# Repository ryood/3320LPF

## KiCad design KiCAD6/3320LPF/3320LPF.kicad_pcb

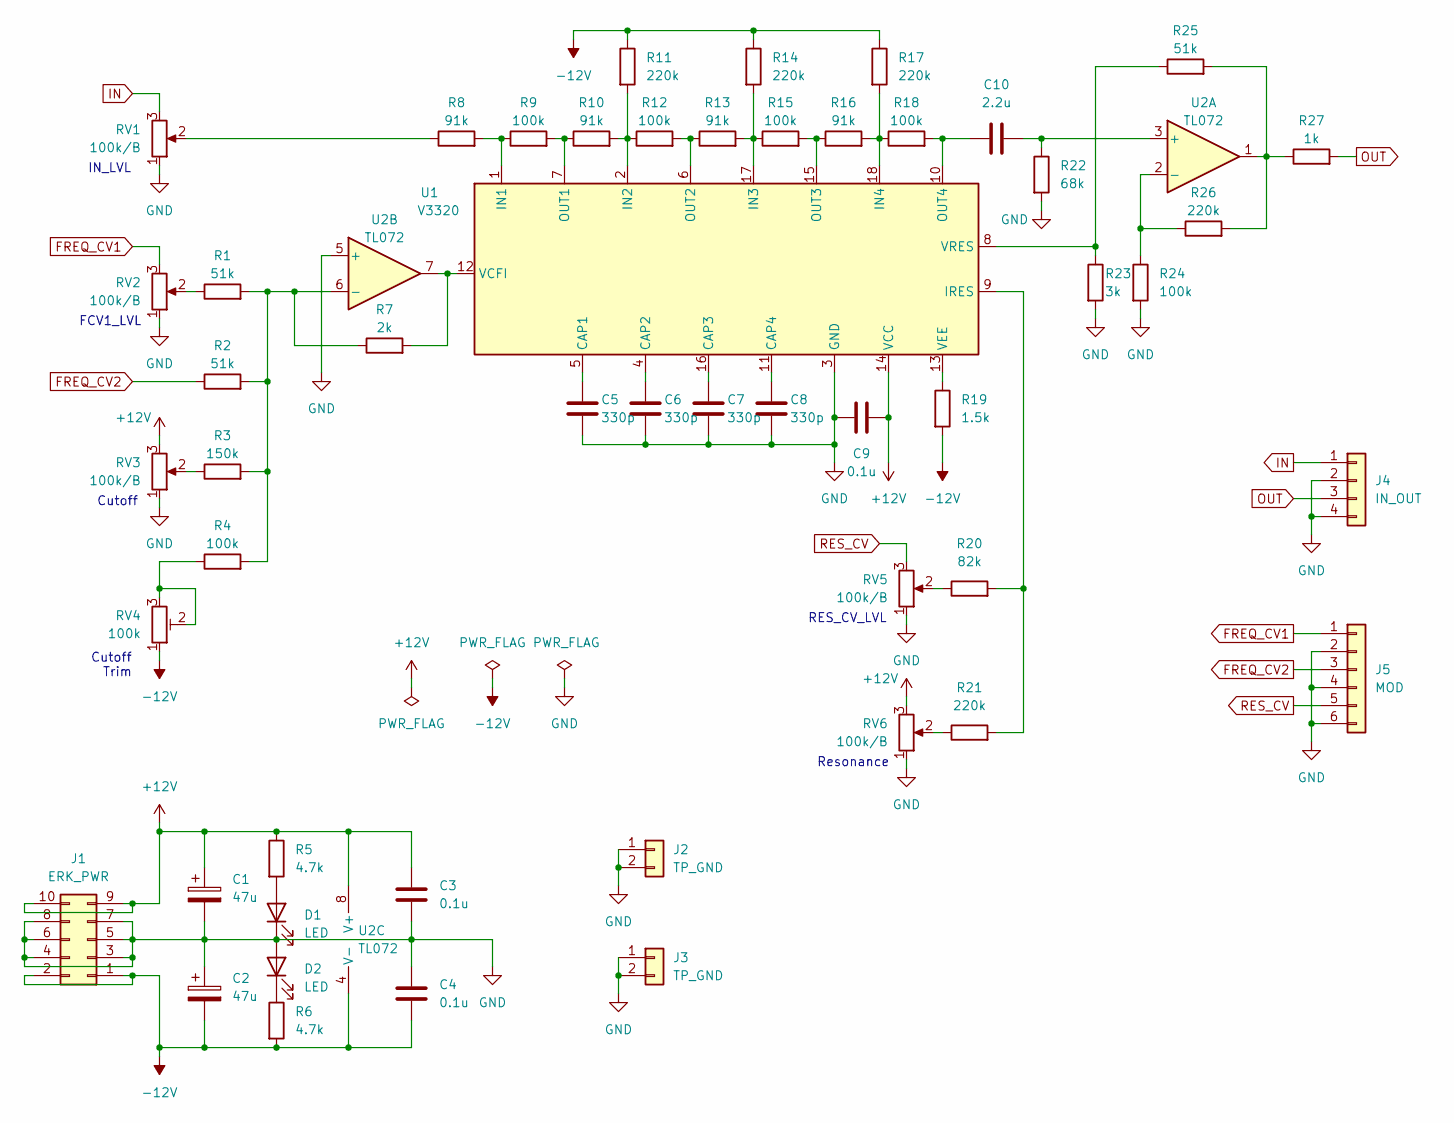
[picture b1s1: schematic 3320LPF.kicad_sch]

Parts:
C1, C2: 47u; CP_Radial_D5.0mm_P2.50mm
C3, C4, C9: 0.1u; C_Disc_D3.0mm_W1.6mm_P2.50mm
C5, C6, C7, C8: 330p; C_Rect_L7.0mm_W3.5mm_P5.00mm
C10: 2.2u; C_Rect_L7.2mm_W7.2mm_P5.00mm_FKS2_FKP2_MKS2_MKP2
D1, D2: LED; LED_D3.0mm
J1: ERK_PWR; IDC-Header_2x05_P2.54mm_Vertical
J2, J3: TP_GND; PinHeader_1x02_P2.54mm_Vertical
J4: IN_OUT; JST_XH_B4B-XH-A_1x04_P2.50mm_Vertical
J5: MOD; JST_XH_B6B-XH-A_1x06_P2.50mm_Vertical
R1, R2, R25: 51k; R_Axial_DIN0207_L6.3mm_D2.5mm_P10.16mm_Horizontal
R3: 150k; R_Axial_DIN0207_L6.3mm_D2.5mm_P10.16mm_Horizontal
R4, R9, R12, R15, R18, R24: 100k; R_Axial_DIN0207_L6.3mm_D2.5mm_P10.16mm_Horizontal
R5, R6: 4.7k; R_Axial_DIN0207_L6.3mm_D2.5mm_P10.16mm_Horizontal
R7: 2k; R_Axial_DIN0207_L6.3mm_D2.5mm_P10.16mm_Horizontal
R8, R10, R13, R16: 91k; R_Axial_DIN0207_L6.3mm_D2.5mm_P10.16mm_Horizontal
R11, R14, R17, R21, R26: 220k; R_Axial_DIN0207_L6.3mm_D2.5mm_P10.16mm_Horizontal
R19: 1.5k; R_Axial_DIN0207_L6.3mm_D2.5mm_P10.16mm_Horizontal
R20: 82k; R_Axial_DIN0207_L6.3mm_D2.5mm_P10.16mm_Horizontal
R22: 68k; R_Axial_DIN0207_L6.3mm_D2.5mm_P10.16mm_Horizontal
R23: 3k; R_Axial_DIN0207_L6.3mm_D2.5mm_P10.16mm_Horizontal
R27: 1k; R_Axial_DIN0207_L6.3mm_D2.5mm_P10.16mm_Horizontal
RV1, RV2, RV3, RV5, RV6: 100k/B; Potentiometer_Alps_RK09Y11_Single_Horizontal
RV4: 100k; Potentiometer_Bourns_3362P_Vertical
U1: V3320; DIP-18_W15.24mm
U2: TL072; DIP-8_W7.62mm_Socket

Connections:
+12V: C1.1, C3.1, C9.2, J1.9, J1.10, R5.1, RV3.3, RV6.3, U1.14 (VCC), U2.8 (V+)
-12V: C2.2, C4.2, J1.1, J1.2, R6.2, R11.1, R14.1, R17.1, R19.2, RV4.1, U2.4 (V-)
FREQ_CV1: J5.1, RV2.3
FREQ_CV2: J5.3, R2.1
GND: C1.2, C2.1, C3.2, C4.1, C5.2, C6.2, C7.2, C8.2, C9.1, D1.1 (K), D2.2 (A), J1.3, J1.4, J1.5, J1.6, J1.7, J1.8, J2.1, J2.2, J3.1, J3.2, J4.2, J4.4, J5.2, J5.4, J5.6, R22.2, R23.2, R24.2, RV1.1, RV2.1, RV3.1, RV5.1, RV6.1, U1.3 (GND), U2.5 (+)
IN: J4.1, RV1.3
unnamed: C5.1, U1.5 (CAP1)
unnamed: C6.1, U1.4 (CAP2)
unnamed: C7.1, U1.16 (CAP3)
unnamed: C8.1, U1.11 (CAP4)
unnamed: C10.1, R18.2, U1.10 (OUT4)
unnamed: C10.2, R22.1, U2.3 (+)
unnamed: D2.1 (K), R6.1
unnamed: R1.1, RV2.2
unnamed: R1.2, R2.2, R3.2, R4.2, R7.1, U2.6 (-)
unnamed: R3.1, RV3.2
unnamed: R4.1, RV4.2, RV4.3
unnamed: D1.2 (A), R5.2
unnamed: R7.2, U1.12 (VCFI), U2.7
unnamed: R8.1, RV1.2
unnamed: R8.2, R9.1, U1.1 (IN1)
unnamed: R9.2, R10.1, U1.7 (OUT1)
unnamed: R10.2, R11.2, R12.1, U1.2 (IN2)
unnamed: R12.2, R13.1, U1.6 (OUT2)
unnamed: R13.2, R14.2, R15.1, U1.17 (IN3)
unnamed: R15.2, R16.1, U1.15 (OUT3)
unnamed: R16.2, R17.2, R18.1, U1.18 (IN4)
unnamed: R19.1, U1.13 (VEE)
unnamed: R20.1, RV5.2
unnamed: R20.2, R21.2, U1.9 (IRES)
unnamed: R21.1, RV6.2
unnamed: R23.1, R25.1, U1.8 (VRES)
unnamed: R24.1, R26.1, U2.2 (-)
unnamed: R25.2, R26.2, R27.1, U2.1
OUT: J4.3, R27.2
RES_CV: J5.5, RV5.3

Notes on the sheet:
Resonance
Cutoff
Cutoff Trim
RES_CV_LVL
IN_LVL
FCV1_LVL

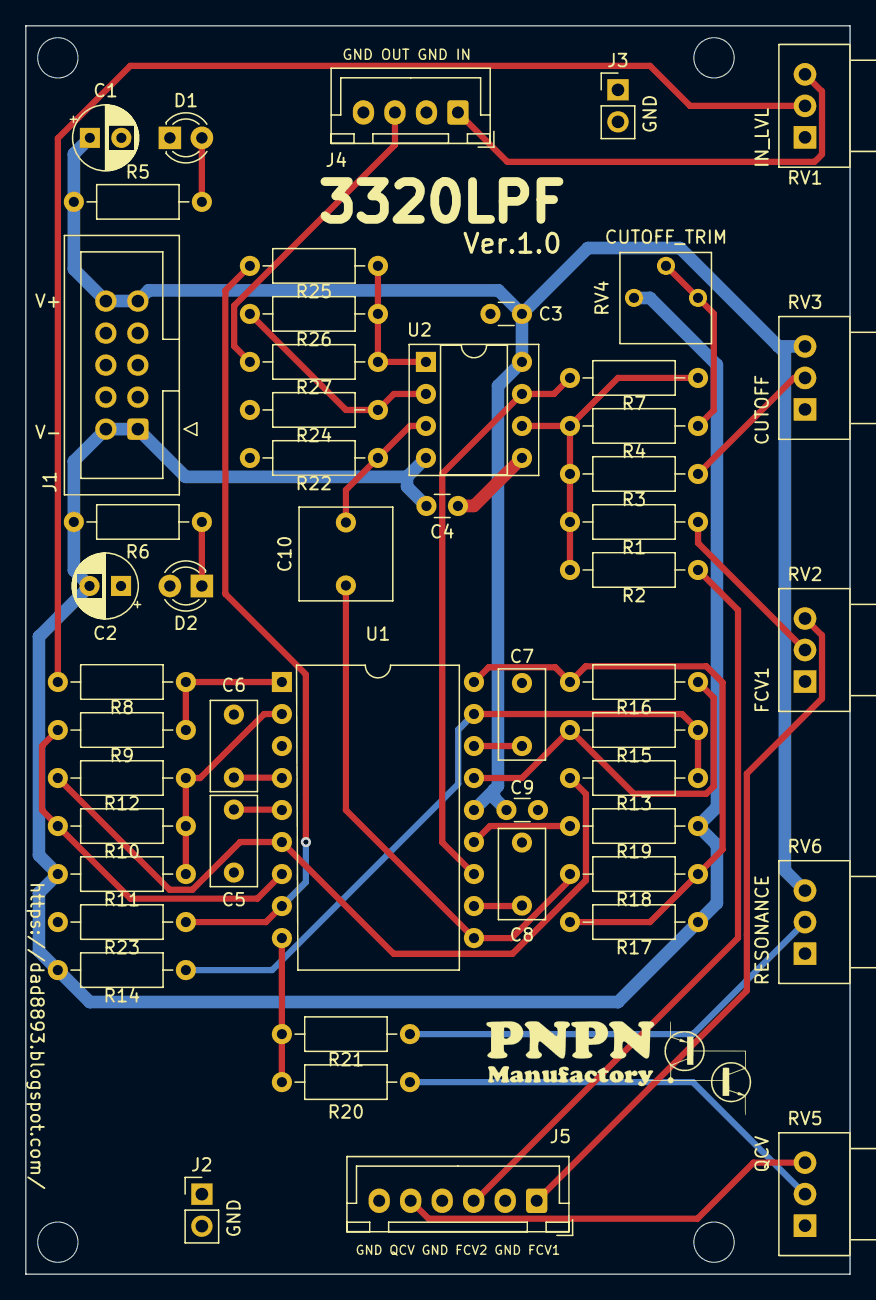
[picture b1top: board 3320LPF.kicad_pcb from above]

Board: 2 copper layers, 65.4 x 99.1 mm, 52 parts (0 on the bottom side), 36 nets.

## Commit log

2022-11-12 Blog
